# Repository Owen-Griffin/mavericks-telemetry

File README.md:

# Westmount Mavericks Telemetry System: MAVT_25
## Laptop Code
- Python Flask web-app with websocket for sending data to frontend
- Logging support to prevent data loss

## Car Unit Code
- Not yet implemented

## Receiver Unit Code
- Not yet implemented

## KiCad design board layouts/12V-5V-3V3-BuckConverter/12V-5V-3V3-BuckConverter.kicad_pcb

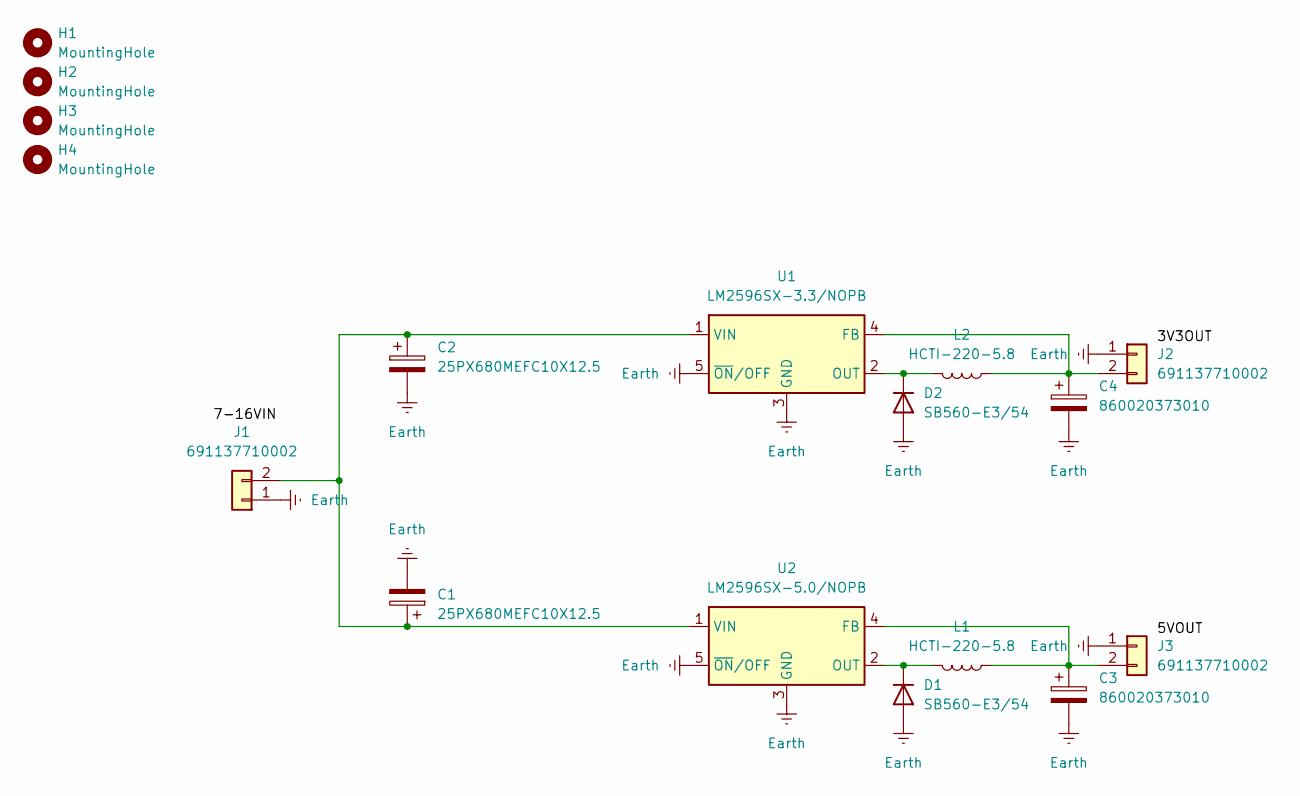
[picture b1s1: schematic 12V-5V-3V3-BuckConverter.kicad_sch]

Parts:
C1, C2: 25PX680MEFC10X12.5; CP_Radial_D10.0mm_P5.00mm
C3, C4: 860020373010; CP_Radial_D6.3mm_P2.50mm
D1, D2: SB560-E3/54; D_DO-27_P12.70mm_Horizontal
H1, H2, H3, H4: MountingHole; MountingHole_2.5mm
J1, J2, J3: 691137710002; TerminalBlock_MaiXu_MX126-5.0-02P_1x02_P5.00mm
L1, L2: HCTI-220-5.8; L_Radial_D14.2mm_P10.00mm_Neosid_SD14
U1: LM2596SX-3.3/NOPB; TO-263-5_TabPin3
U2: LM2596SX-5.0/NOPB; TO-263-5_TabPin3

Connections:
Earth: C1.2, C2.2, C3.2, C4.2, D1.2 (A), D2.2 (A), J1.1, J2.1, J3.1, U1.3 (GND), U1.5 (~ON/OFF), U2.3 (GND), U2.5 (~ON/OFF)
unnamed: D1.1 (K), L1.2, U2.2 (OUT)
unnamed: D2.1 (K), L2.2, U1.2 (OUT)
unnamed: C1.1, C2.1, J1.2, U1.1 (VIN), U2.1 (VIN)
unnamed: C4.1, J2.2, L2.1, U1.4 (FB)
unnamed: C3.1, J3.2, L1.1, U2.4 (FB)

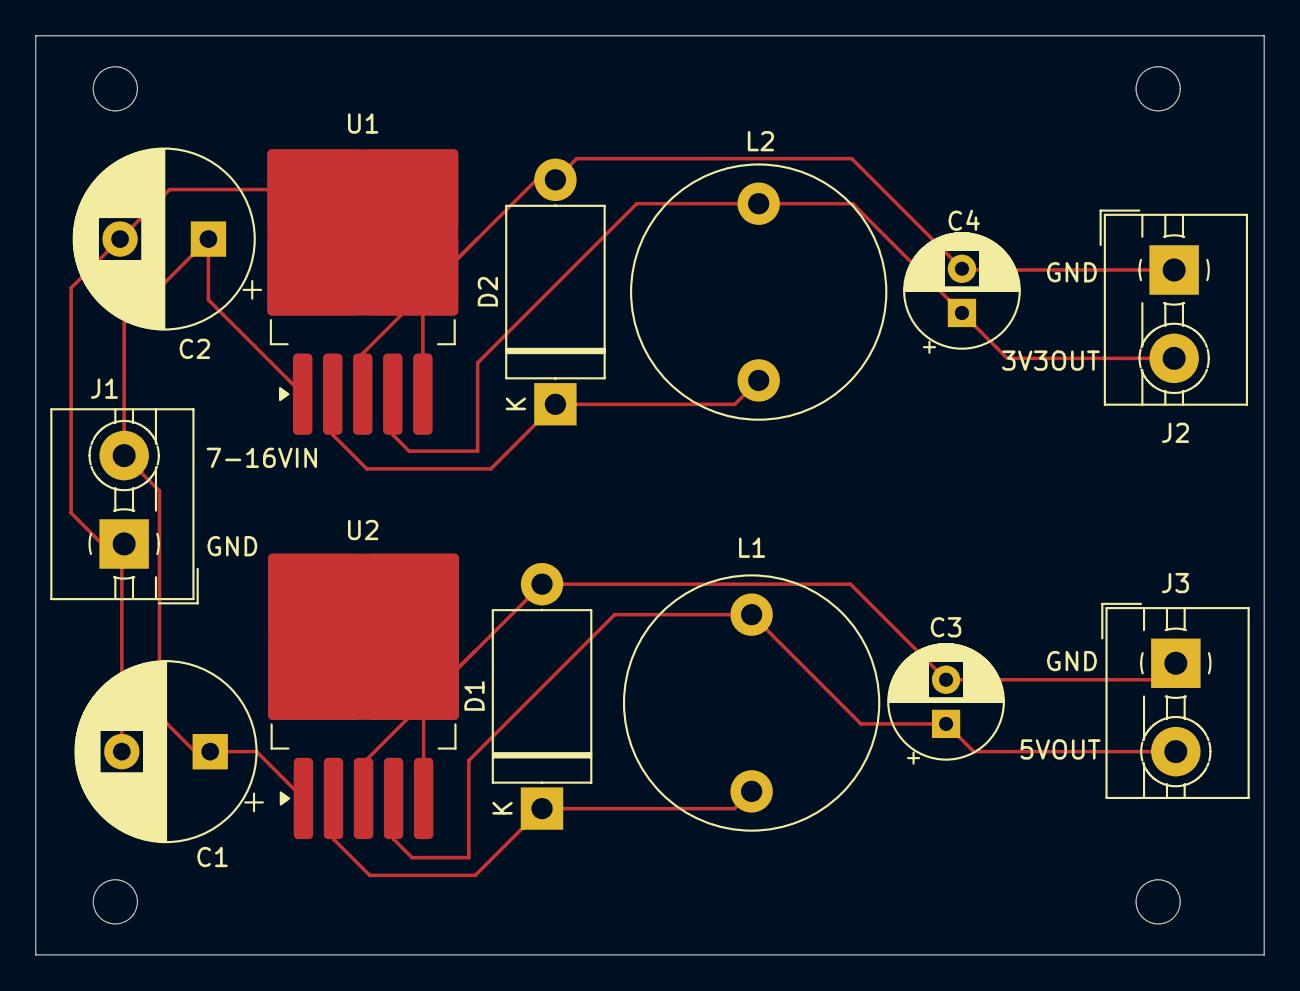
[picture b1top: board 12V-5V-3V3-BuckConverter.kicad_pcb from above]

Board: 2 copper layers, 69.5 x 52.0 mm, 17 parts (0 on the bottom side), 6 nets.

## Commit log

2024-10-17 inital code
2024-10-17 continue UI development
2024-10-17 add remaining graphs
2024-10-19 general development
2024-10-19 update gitignore
2024-10-21 begin implementing car code
2024-10-21 Create logs dir
2024-10-21 update data reciving
2024-10-21 Revert "update data reciving" SAVE THE MAIN FILE I DELETED This reverts commit f735ff1a49cb3f01e22cdba629add749ddcbeefe.
2024-10-21 update data reciving, delete temp file
2024-10-23 fix default value for wheelRPM
2024-12-01 add nrf testing thingy, will be deleted later
2024-12-02 update logging
2024-12-02 add maximize for charts
2024-12-02 add doctype declaration
2024-12-02 add settings modal
2024-12-02 add max length setting, refactor graph updating, add random temp values
2024-12-02 refactor updating to remove unessisary function
2024-12-02 clean up js
2024-12-02 add comments, remove unnecessary jsonify import
2024-12-15 add first draft board design
2024-12-15 update board layout
2024-12-21 update board
2024-12-21 create receiver unit code, create test programs to send/receive nRF transmissions
2024-12-21 remove old test code
2024-12-21 restructure file org
2024-12-21 update gitignore to fit new file structure
2024-12-21 move files, fix spelling error
2024-12-21 create screen test program
2024-12-22 improve test programs
2024-12-29 implement i2c scanner and screen tester programs, begin implement car unit code
2024-12-31 clean up code
2024-12-31 bug fixes
2024-12-31 bug fix
2025-01-01 create 12V -> 5/3.3v buck converter PCB design
2025-01-25 remove old boards, add cors headers
2025-03-19 fix the awful code
2025-03-20 add license info + debug line
2025-03-24 add webserver test code + add to main code
